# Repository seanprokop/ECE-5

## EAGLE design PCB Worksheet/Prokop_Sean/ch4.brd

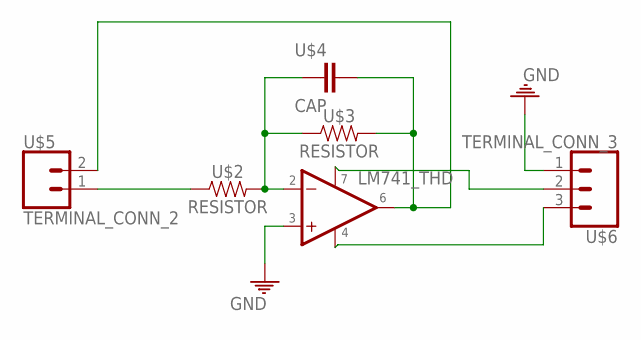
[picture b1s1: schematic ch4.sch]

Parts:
U$1: IC-LM741
U$2, U$3: RESISTOR
U$4: CAP; CAP-TH
U$5: TERMINAL_CONN_2
U$6: TERMINAL_CONN_3; TERMINAL-CONN_3

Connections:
GND: U$1.3 (+IN), U$6.1
unnamed: U$2.1, U$5.1
unnamed: U$1.2 (-IN), U$2.2, U$3.1, U$4.1
unnamed: U$1.7, U$6.2
unnamed: U$1.6 (OUT), U$3.2, U$4.2, U$5.2
unnamed: U$1.4, U$6.3

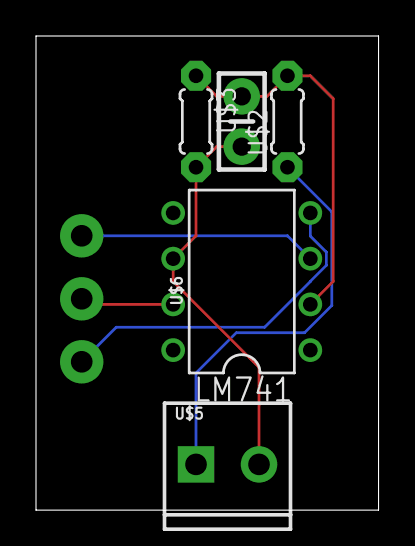
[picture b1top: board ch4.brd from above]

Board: 2 copper layers, 19.0 x 26.3 mm, 6 parts (0 on the bottom side), 6 nets.

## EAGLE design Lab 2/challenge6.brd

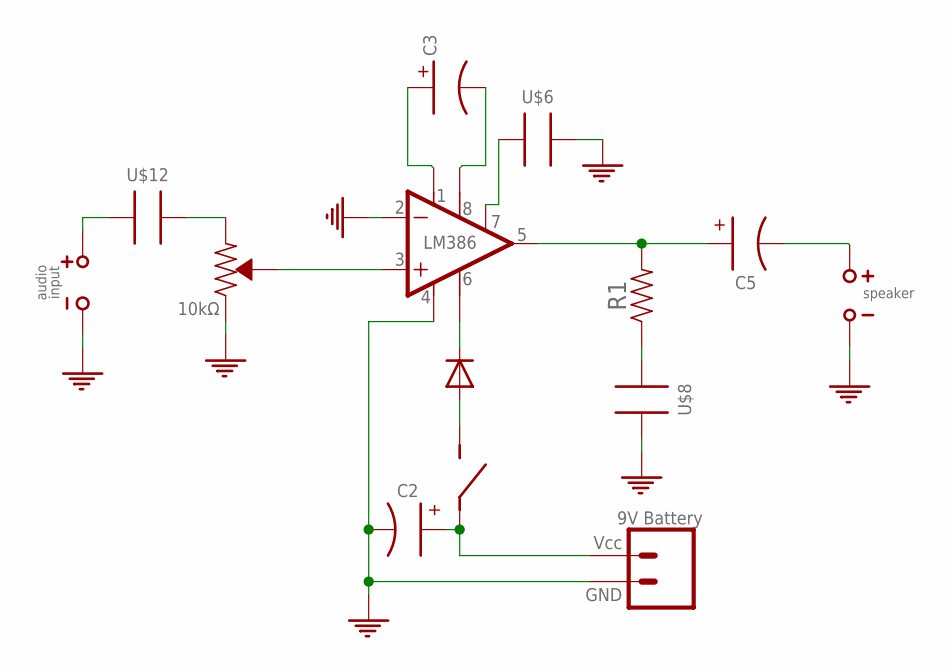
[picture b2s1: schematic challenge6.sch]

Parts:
IC1: LM386; LM386_DIP08
U$1: DIODE; DIODE_1N4001
U$2: SWITCH
U$3: C2_100UF; CAP_100UF_POLARIZED
U$4: 9V_BATTERY; 9V_BATT
U$5: C3_10UF; CAP_10UF_POLARIZED
U$6, U$8, U$12: C_0.1UF; CAP_0.1UF
U$7: R1_10Ω
U$9: C5_1000UF; CAP_1000UF_POLARIZED
U$10: SPEAKER
U$11: POTENTIOMETER_10KΩ; POT_10KΩ
U$13: AUDIO_INPUT

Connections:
GND: IC1.2 (-IN_2), IC1.4 (V-_4), U$3.- (K), U$4.-, U$6.P$2 (2), U$8.P$2 (2), U$10.-, U$11.3 (CW_MINVOL), U$13.-
unnamed: IC1.6 (V+_6), U$1.C
unnamed: U$1.A, U$2.2
unnamed: U$2.1, U$3.+ (A), U$4.+
unnamed: IC1.8 (GAIN2_8), U$5.- (K)
unnamed: IC1.1 (GAIN1_1), U$5.+ (A)
unnamed: IC1.7 (BYPASS_7), U$6.P$1 (1)
unnamed: U$9.- (K), U$10.+
unnamed: IC1.5 (OUT_5), U$7.2, U$9.+ (A)
unnamed: U$7.1, U$8.P$1 (1)
unnamed: U$12.P$1 (1), U$13.+
unnamed: U$11.1 (CCW_MAXVOL), U$12.P$2 (2)
unnamed: IC1.3 (+IN_3), U$11.2 (WIPER)

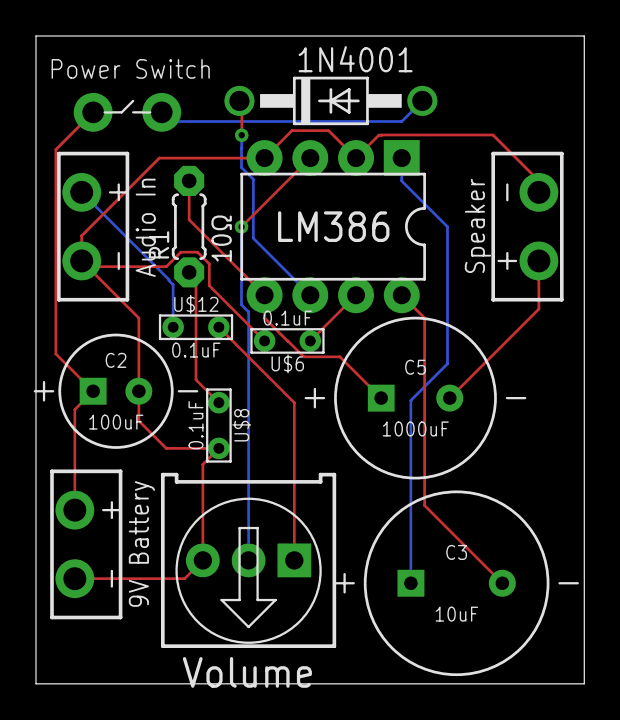
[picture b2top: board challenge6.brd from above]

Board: 2 copper layers, 30.5 x 36.0 mm, 14 parts (0 on the bottom side), 13 nets.

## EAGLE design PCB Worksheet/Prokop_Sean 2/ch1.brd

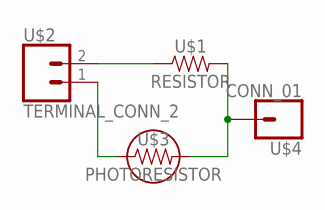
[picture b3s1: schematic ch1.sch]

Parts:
U$1: RESISTOR
U$2: TERMINAL_CONN_2
U$3: PHOTORESISTOR
U$4: CONN_01; 1X01

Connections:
unnamed: U$1.1, U$2.2
unnamed: U$1.2, U$3.P$2 (2), U$4.1
unnamed: U$2.1, U$3.P$1 (1)

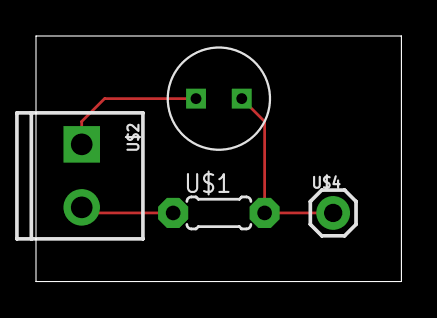
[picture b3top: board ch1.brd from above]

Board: 2 copper layers, 20.3 x 13.6 mm, 4 parts (0 on the bottom side), 3 nets.

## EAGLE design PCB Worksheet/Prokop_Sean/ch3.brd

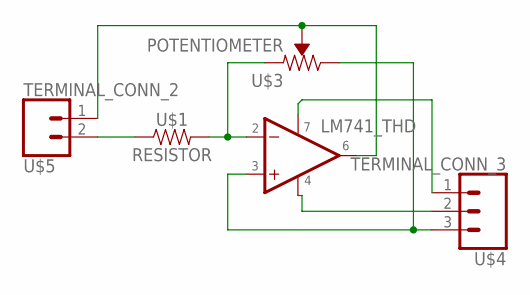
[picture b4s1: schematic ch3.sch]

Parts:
U$1: RESISTOR
U$2: IC-LM741
U$3: POTENTIOMETER
U$4: TERMINAL_CONN_3; TERMINAL-CONN_3
U$5: TERMINAL_CONN_2

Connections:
unnamed: U$1.2, U$2.2 (-IN), U$3.1 (CCW)
unnamed: U$2.6 (OUT), U$3.2 (WIPER), U$5.1
unnamed: U$2.3 (+IN), U$3.3 (CW), U$4.3
unnamed: U$2.4, U$4.2
unnamed: U$2.7, U$4.1
unnamed: U$1.1, U$5.2

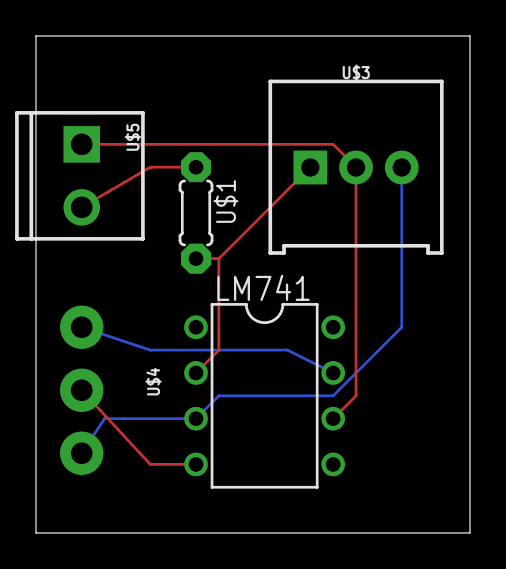
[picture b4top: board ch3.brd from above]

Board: 2 copper layers, 24.1 x 27.6 mm, 5 parts (0 on the bottom side), 6 nets.

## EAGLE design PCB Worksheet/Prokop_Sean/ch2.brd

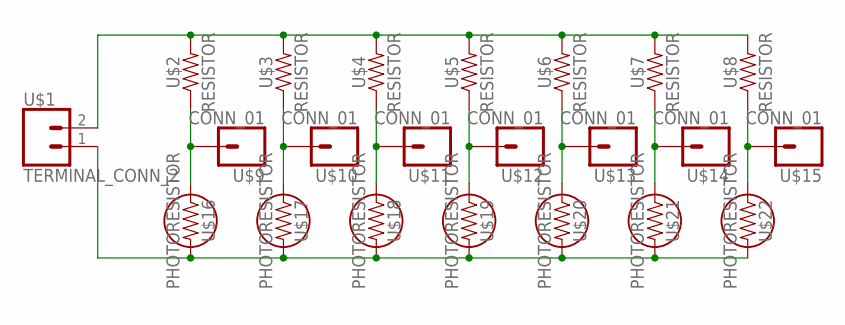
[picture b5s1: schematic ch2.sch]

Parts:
U$1: TERMINAL_CONN_2
U$2, U$3, U$4, U$5, U$6, U$7, U$8: RESISTOR
U$9, U$10, U$11, U$12, U$13, U$14, U$15: CONN_01; 1X01
U$16, U$17, U$18, U$19, U$20, U$21, U$22: PHOTORESISTOR

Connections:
unnamed: U$1.2, U$2.2, U$3.2, U$4.2, U$5.2, U$6.2, U$7.2, U$8.2
unnamed: U$2.1, U$9.1, U$16.P$1 (1)
unnamed: U$3.1, U$10.1, U$17.P$1 (1)
unnamed: U$4.1, U$11.1, U$18.P$1 (1)
unnamed: U$5.1, U$12.1, U$19.P$1 (1)
unnamed: U$6.1, U$13.1, U$20.P$1 (1)
unnamed: U$7.1, U$14.1, U$21.P$1 (1)
unnamed: U$8.1, U$15.1, U$22.P$1 (1)
unnamed: U$1.1, U$16.P$2 (2), U$17.P$2 (2), U$18.P$2 (2), U$19.P$2 (2), U$20.P$2 (2), U$21.P$2 (2), U$22.P$2 (2)

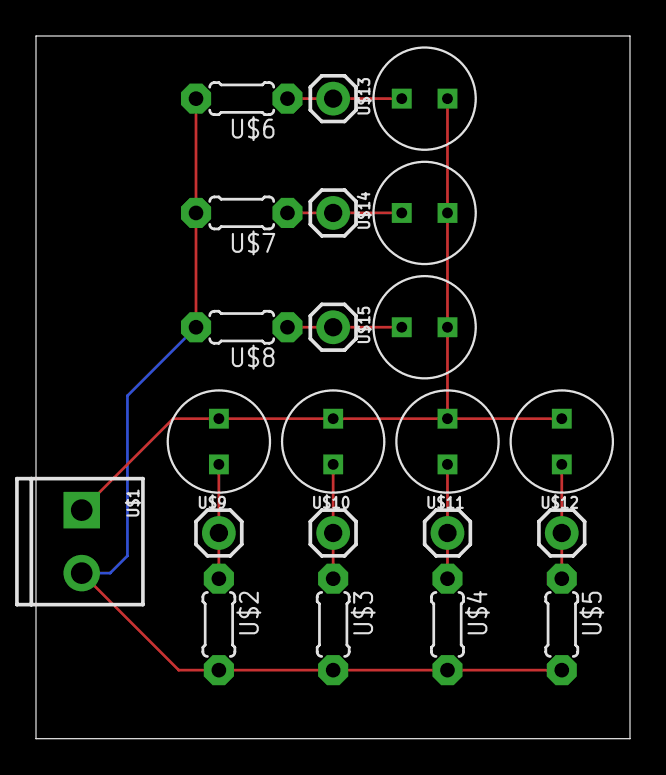
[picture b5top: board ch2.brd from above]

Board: 2 copper layers, 33.0 x 39.0 mm, 22 parts (0 on the bottom side), 9 nets.

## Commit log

2019-01-25 Importing ECE 5 files
2019-01-26 Organized files into folders
2019-01-26 Added laser cutting worksheet stuff
2019-02-12 Lab 3 First Challenge Matlab
    Uploading screenshots and matlab script for Challenge 2A
2019-02-13 Adding new files from mac
2019-02-13 Lab 3 part 1 files
2019-02-15 Adding part 2 of Lab 3 for ECE 5, and cleaning up the directory
2019-02-22 Adding lab 4 files
